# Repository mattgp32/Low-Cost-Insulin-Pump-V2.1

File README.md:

# Ultra Low-Cost Insulin Pump

This Git repository represents the final result of multiple design iterations of a low-cost insulin pump I have designed as part of my studies in medical device development. The repository contains files for hardware, both electrical and mechanical, and firmware. I have also included a BOM to make ordering of components easier if anyone wishes to replicate this design. The device has been tested in humans, in a small clinical trial, and a write-up of the results was published [here](https://pmc.ncbi.nlm.nih.gov/articles/PMC11292867/).

## Overview

The files for this device are split into four main areas: electrical hardware, mechanical hardware, android application, and firmware. This README contains a subsection for each of these aspects, including build instructions, initial setup, and usage. A complete exploded assembly for the device is shown in the image below:

### Electrical Hardware
PCB schematics and layout were created in KiCad, so you will need to install this to view/edit/order some assemblies. KiCad can be downloaded [here](https://www.kicad.org/download/). I added some components by hand to reduce costs; however I acknowledge not everyone would be comfortable to do so. Therefore, I'll be uploading an EasyEDA file soon which can be uploaded to JLCPCB, and allow you to order an assembled board more easily. Expect the total cost of an assembled board to be around US$30.

This PCB utilises an ESP32-S3 SOC as its MCU, and delivers the following key features for the low-cost pump:

1. Wireless communication via BLE
2. Stepper motor control thorugh interface with DRV8846
3. Li-Po charging through interface with MCP78371 through USB C 2.0
4. ADC monitoring of battery level 
5. ADC monitoring of linear potentiometer to determine position.
6. LEDs for user feedback and monitoring

#### Build Instructions

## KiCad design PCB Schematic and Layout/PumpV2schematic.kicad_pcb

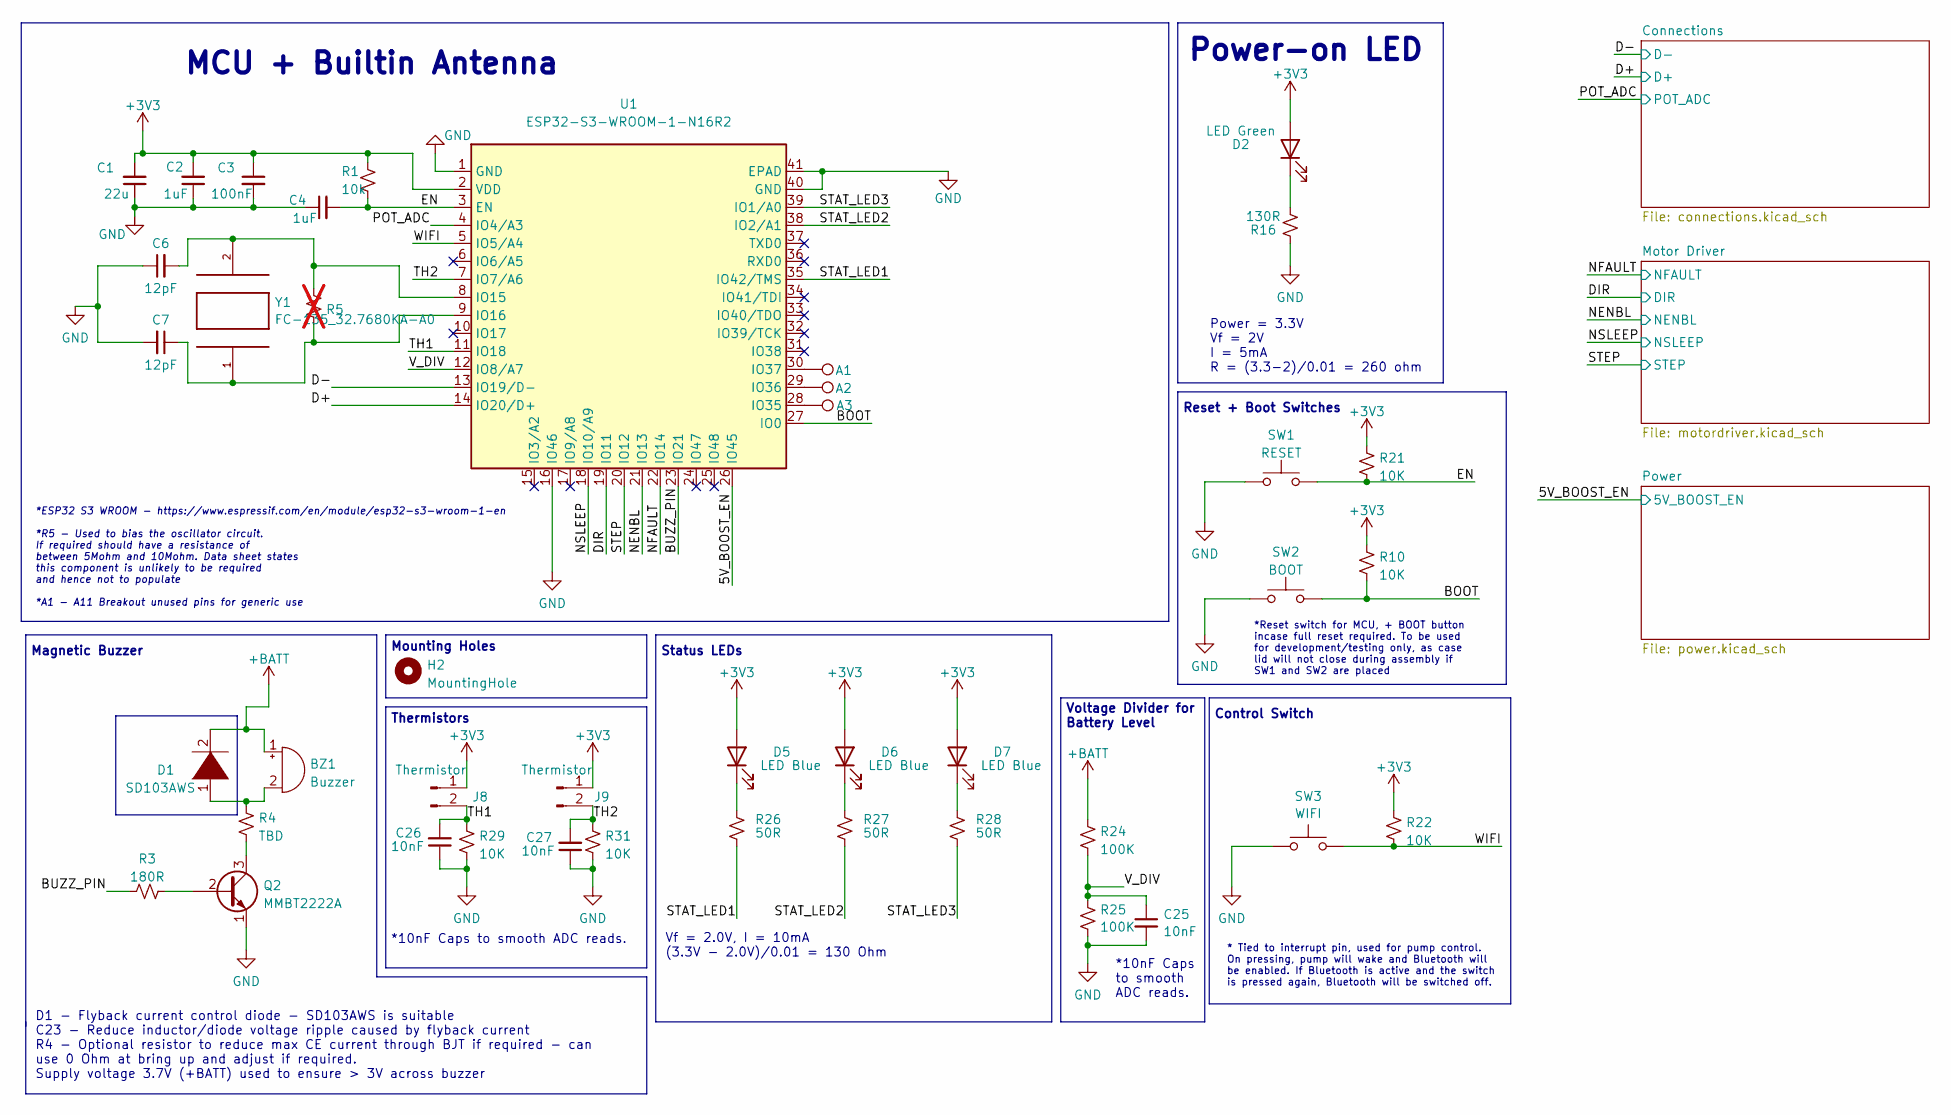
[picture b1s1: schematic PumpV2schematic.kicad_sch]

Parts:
A1, A2, A3: A0; TestPoint_THTPad_1.0x1.0mm_Drill0.5mm
BZ1: Buzzer; ST-0503 BUZZER
C1: 22u; C_0402_1005Metric; LCSC C2179118
C2, C4: 1uF; C_0402_1005Metric; LCSC C2887021
C3: 100nF; C_0402_1005Metric; LCSC C913614
C6, C7: 12pF; C_0402_1005Metric; LCSC C2235030
C25, C26, C27: 10nF; C_0402_1005Metric; LCSC C2167195
D1: SD103AWS; D_SOD-323; LCSC C181207
D2: LED Green; LED_0603_1608Metric; LCSC C84264
D5, D6, D7: LED Blue; LED_0603_1608Metric; LCSC C72041
H2: MountingHole; MountingHole_2.2mm_M2_ISO7380_Pad_TopBottom
J8, J9: Thermistor; PinHeader_1x02_P1.27mm_Vertical
Q2: MMBT2222A; SOT-23; LCSC C2891810
R1: 10k; R_0402_1005Metric; LCSC C25744
R3: 180R; R_0402_1005Metric; LCSC C911962
R4: TBD; R_0402_1005Metric; LCSC C17168
R5: TBD; R_0402_1005Metric; not fitted
R10, R21, R22, R29, R31: 10K; R_0402_1005Metric; LCSC C25744
R16: 130R; R_0402_1005Metric; LCSC C270649
R24, R25: 100K; R_0402_1005Metric; LCSC C319963
R26, R27, R28: 50R; R_0402_1005Metric; LCSC C477760
SW1: RESET; SW_DIP_SPSTx01_Slide_6.7x4.1mm_W6.73mm_P2.54mm_LowProfile_J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
SW2: BOOT; SW_DIP_SPSTx01_Slide_6.7x4.1mm_W6.73mm_P2.54mm_LowProfile_J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
SW3: WIFI; SW_DIP_SPSTx01_Slide_6.7x4.1mm_W6.73mm_P2.54mm_LowProfile_J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
U1: ESP32-S3-WROOM-1-N16R2; ESP32-S3-WROOM-1; LCSC C2913202
Y1: FC-135_32.7680KA-A0; XTAL_FC-135_32.7680KA-A0; LCSC C841881

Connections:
+3V3: C1.2, C2.2, C3.1, D2.2 (A), D5.2 (A), D6.2 (A), D7.2 (A), J8.1, J9.1, R1.1, R10.1, R21.1, R22.1, U1.2 (VDD); also elsewhere on the board
+BATT: BZ1.1 (-), D1.2 (A), R24.1; also elsewhere on the board
/5V_BOOST_EN: U1.26 (IO45); also elsewhere on the board
/BOOT: R10.2, SW2.2, U1.27 (IO0)
/BUZZ_PIN: R3.1, U1.23 (IO21)
/D+: U1.14 (IO20/D+); also elsewhere on the board
/D-: U1.13 (IO19/D-); also elsewhere on the board
/DIR: U1.19 (IO11); also elsewhere on the board
/EN: C4.2, R1.2, R21.2, SW1.2, U1.3 (EN)
/NENBL: U1.21 (IO13); also elsewhere on the board
/NFAULT: U1.22 (IO14); also elsewhere on the board
/NSLEEP: U1.18 (IO10/A9); also elsewhere on the board
/POT_ADC: U1.4 (IO4/A3); also elsewhere on the board
/STAT_LED1: R26.2, U1.35 (IO42/TMS)
/STAT_LED2: R27.2, U1.38 (IO2/A1)
/STAT_LED3: R28.2, U1.39 (IO1/A0)
/STEP: U1.20 (IO12); also elsewhere on the board
/TH1: C26.2, J8.2, R29.1, U1.11 (IO18)
/TH2: C27.2, J9.2, R31.1, U1.7 (IO7/A6)
/V_DIV: C25.1, R24.2, R25.1, U1.12 (IO8/A7)
/WIFI: R22.2, SW3.2, U1.5 (IO5/A4)
GND: C1.1, C2.1, C3.2, C4.1, C6.1, C7.2, C25.2, C26.1, C27.1, Q2.1 (E), R16.2, R25.2, R29.2, R31.2, SW1.1, SW2.1, SW3.1, U1.1 (GND), U1.16 (IO46), U1.40 (GND), U1.41 (EPAD); also elsewhere on the board
unnamed 24: BZ1.2 (+), D1.1 (K), R4.2; also elsewhere on the board
unnamed: D2.1 (K), R16.1
unnamed: D5.1 (K), R26.1
unnamed: D6.1 (K), R27.1
unnamed: D7.1 (K), R28.1
unnamed: Q2.2 (B), R3.2
unnamed: Q2.3 (C), R4.1
unnamed: C6.2, R5.1, U1.8 (IO15), Y1.2
unnamed: C7.1, R5.2, U1.9 (IO16), Y1.1
unnamed: A3.1, U1.28 (IO35)
unnamed: A2.1, U1.29 (IO36)
unnamed: A1.1, U1.30 (IO37)

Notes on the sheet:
Status LEDs
*10nF Caps to smooth ADC reads.
Magnetic Buzzer
Power = 3.3V Vf = 2V I = 5mA R = (3.3-2)/0.01 = 260 ohm
Reset + Boot Switches
*10nF Caps to smooth ADC reads.
MCU + Builtin Antenna
Thermistors
*ESP32 S3 WROOM - https://www.espressif.com/en/module/esp32-s3-wroom-1-en *R5 - Used to bias the oscillator circuit. If required should have a resistance of between 5Mohm and 10Mohm. Data sheet states this component is unlikely to be required and hence not to populate *A1 - A11 Breakout unused pins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
Vf = 2.0V, I = 10mA (3.3V - 2.0V)/0.01 = 130 Ohm
Voltage Divider for Battery Level
Power-on LED
* Tied to interrupt pin, used for pump control. On pressing, pump will wake and Bluetooth will be enabled. If Bluetooth is active and the switch is pressed again, Bluetooth will be switched off.
Control Switch
*Reset switch for MCU, + BOOT button incase full reset required. To be used for development/testing only, as case lid will not close during assembly if SW1 and SW2 are placed
Mounting Holes
D1 - Flyback current control diode - SD103AWS is suitable C23 - Reduce inductor/diode voltage ripple caused by flyback current R4 - Optional resistor to reduce max CE current through BJT if required - can use 0 Ohm at bring up and adjust if required. Supply voltage 3.7V (+BATT) used to ensure > 3V 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

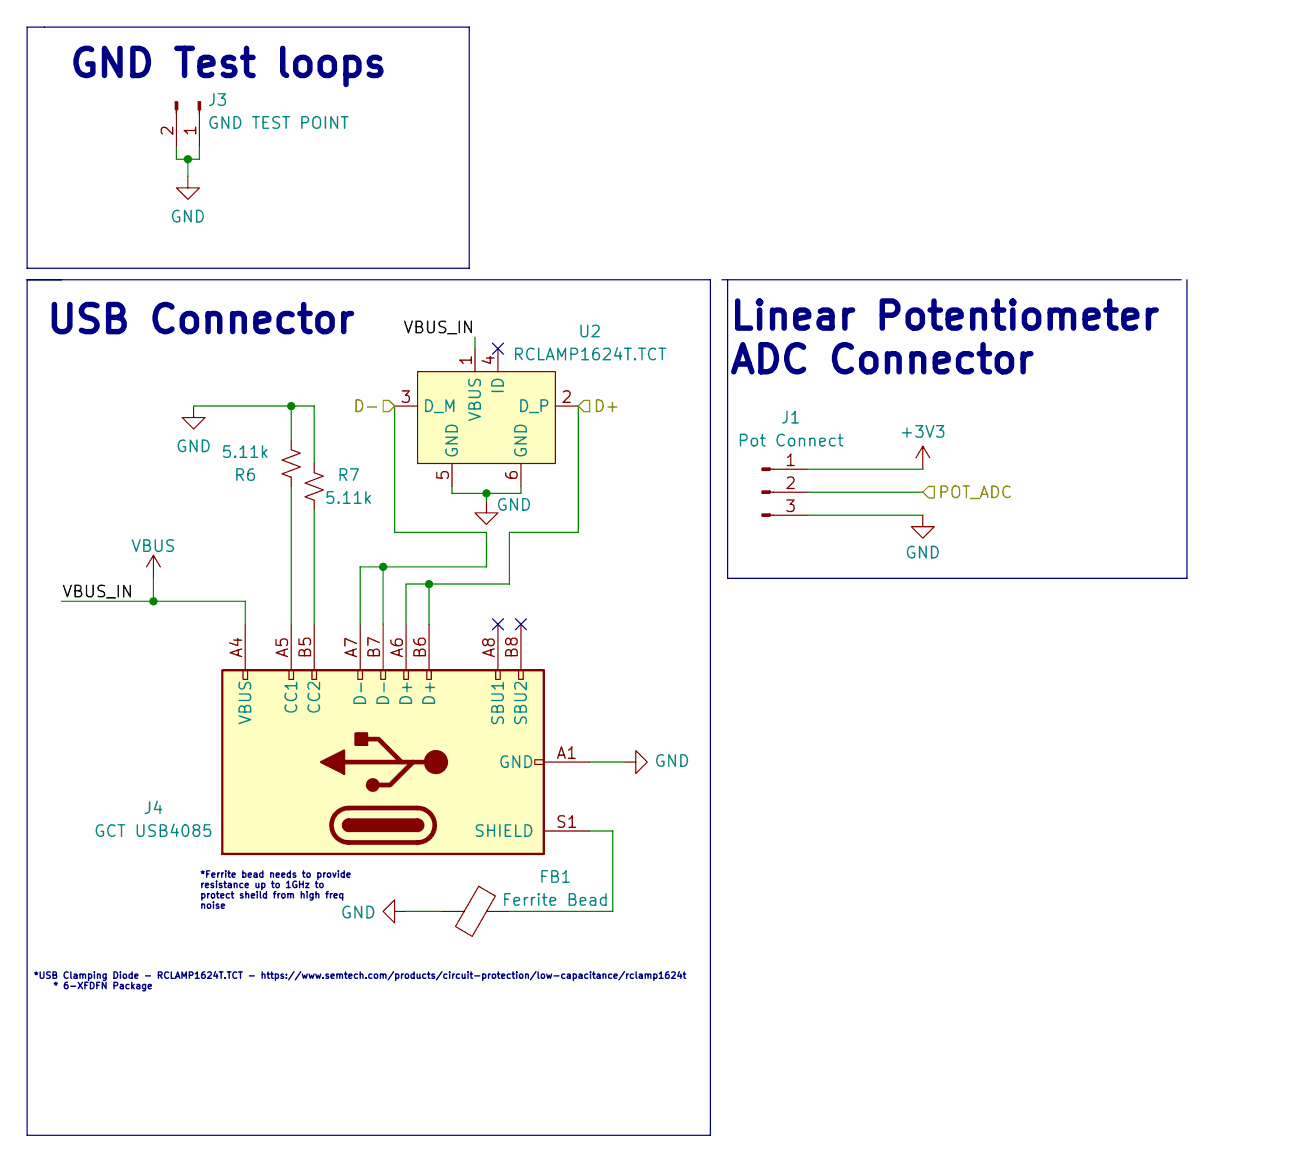
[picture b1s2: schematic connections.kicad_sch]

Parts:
FB1: Ferrite Bead; L_0402_1005Metric; LCSC C21516
J1: Pot Connect; PinHeader_1x03_P1.00mm_Vertical
J3: GND TEST POINT; PinHeader_1x02_P1.27mm_Vertical
J4: GCT USB4085; USB_C_Receptacle_GCT_USB4085
R6: 5.11k; R_0402_1005Metric; LCSC C310235
R7: 5.11k; R_0402_1005Metric
U2: RCLAMP1624T.TCT; SLP1710P4T; LCSC C1973485

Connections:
+3V3: J1.1; also elsewhere on the board
/D+: J4.A6 (D+), J4.B6 (D+), U2.2 (D_P); also elsewhere on the board
/D-: J4.A7 (D-), J4.B7 (D-), U2.3 (D_M); also elsewhere on the board
/POT_ADC: J1.2; also elsewhere on the board
GND: FB1.2, J1.3, J3.1, J3.2, J4.A1 (GND), J4.A12 (GND), J4.B1 (GND), J4.B12 (GND), R6.2, R7.2, U2.5 (GND), U2.6 (GND); also elsewhere on the board
unnamed: J4.A5 (CC1), R6.1
unnamed: J4.B5 (CC2), R7.1
unnamed: FB1.1, J4.S1 (SHIELD)
VBUS: J4.A4 (VBUS), J4.A9 (VBUS), J4.B4 (VBUS), J4.B9 (VBUS), U2.1 (VBUS); also elsewhere on the board

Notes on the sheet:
Linear Potentiometer ADC Connector
*USB Clamping Diode - RCLAMP1624T.TCT - https://www.semtech.com/products/circuit-protection/low-capacitance/rclamp1624t * 6-XFDFN Package
*Ferrite bead needs to provide resistance up to 1GHz to protect sheild from high freq noise
USB Connector
GND Test loops

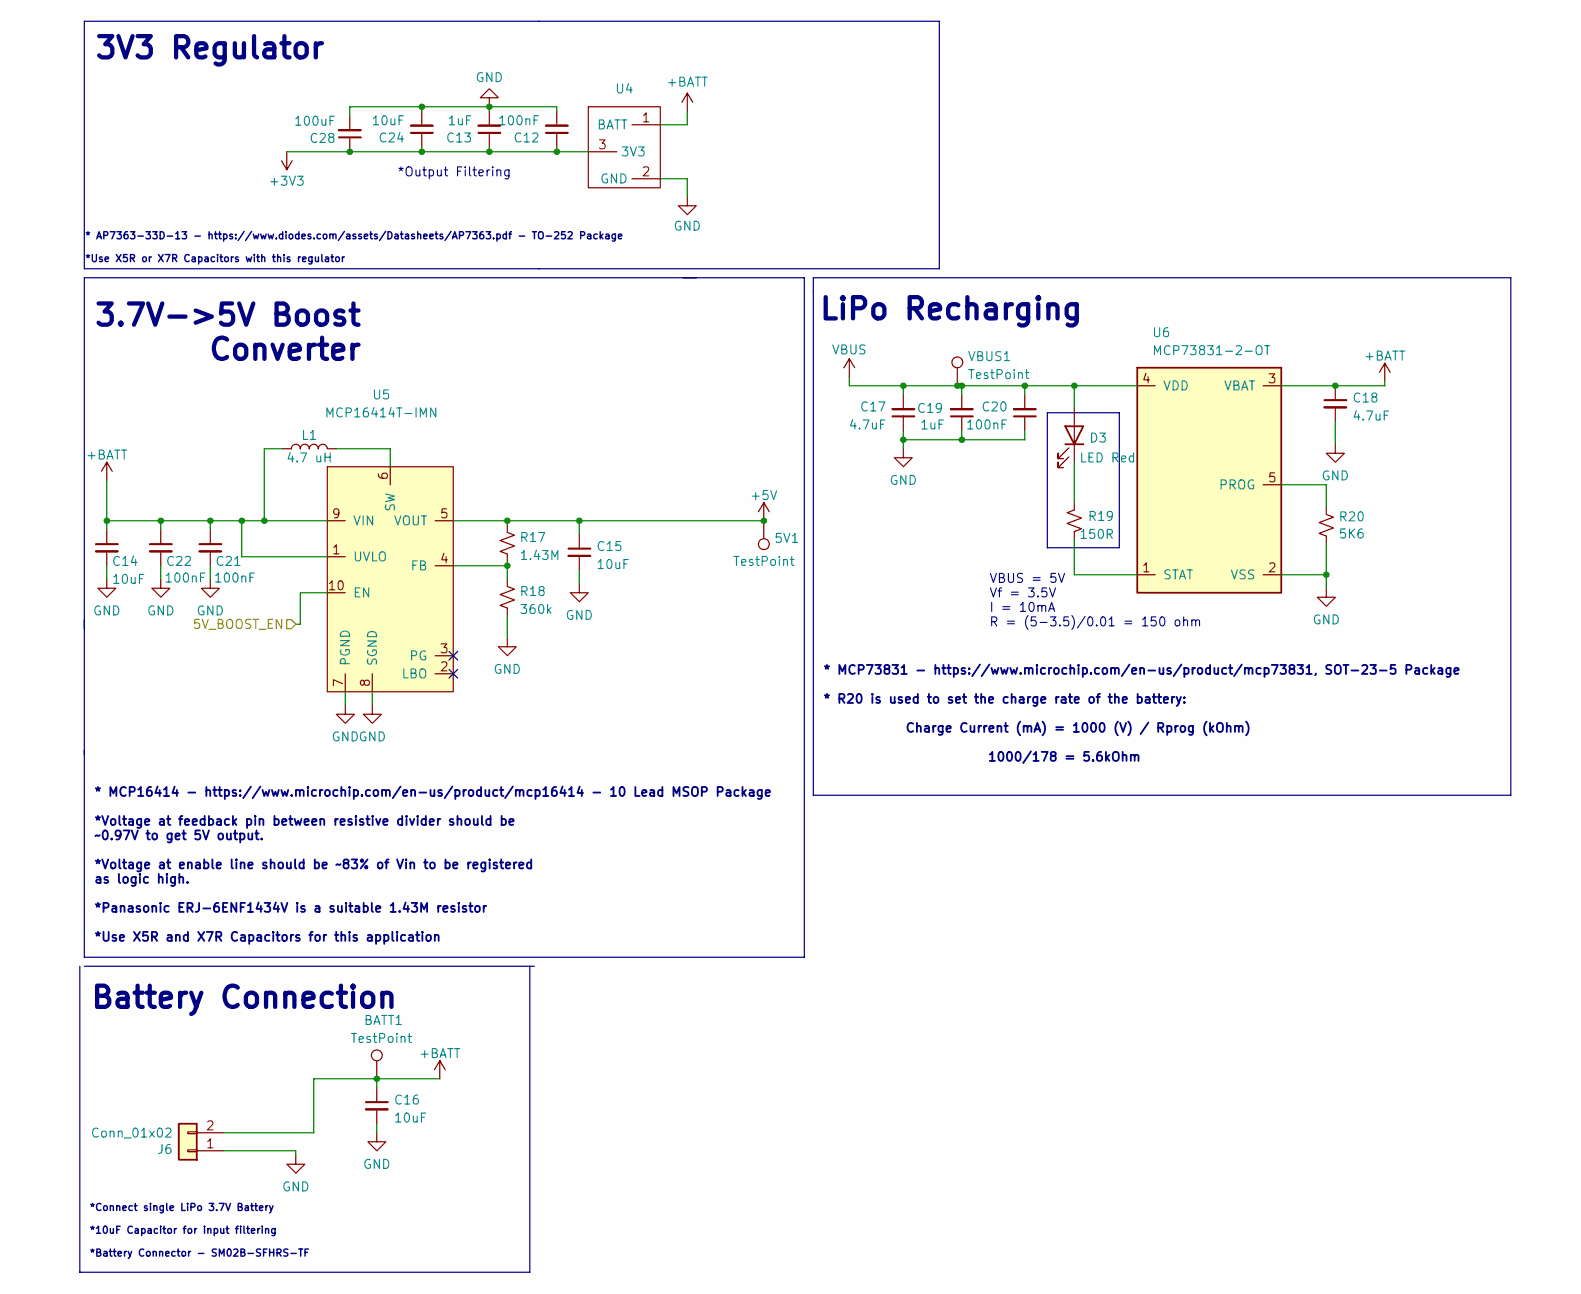
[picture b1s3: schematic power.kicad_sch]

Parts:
5V1: TestPoint; TestPoint_Pad_1.0x1.0mm
BATT1: TestPoint; TestPoint_Pad_1.0x1.0mm
C12, C20, C21, C22: 100nF; C_0402_1005Metric; LCSC C913614
C13, C19: 1uF; C_0402_1005Metric; LCSC C2887021
C14, C15, C16, C24: 10uF; C_0402_1005Metric; LCSC C1864622
C17, C18: 4.7uF; C_0402_1005Metric; LCSC C723999
C28: 100uF; C_1210_3225Metric; LCSC C2762605
D3: LED Red; LED_0603_1608Metric; LCSC C2286
J6: Conn_01x02; PinHeader_1x02_P1.27mm_Vertical
L1: 4.7 uH; L_1008_2520Metric; LCSC C2981204
R17: 1.43M; R_0402_1005Metric; LCSC C368342
R18: 360k; R_0402_1005Metric; LCSC C413117
R19: 150R; R_0402_1005Metric; LCSC C3015763
R20: 5K6; R_0402_1005Metric; LCSC C174239
U4: DPAK; LCSC C108723
U5: MCP16414T-IMN; SOP50P490X110-10N; LCSC C1518054
U6: MCP73831-2-OT; SOT-23-5; LCSC C625597
VBUS1: TestPoint; TestPoint_Pad_1.0x1.0mm

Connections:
+3V3: C12.1, C13.1, C24.1, C28.1, U4.3 (3V3); also elsewhere on the board
+5V: 5V1.1, C15.1, R17.1, U5.5 (VOUT); also elsewhere on the board
+BATT: BATT1.1, C14.1, C16.1, C18.1, C21.1, C22.1, J6.2, L1.1, U4.1 (BATT), U5.1 (UVLO), U5.9 (VIN), U6.3 (VBAT); also elsewhere on the board
/5V_BOOST_EN: U5.10 (EN); also elsewhere on the board
GND: C12.2, C13.2, C14.2, C15.2, C16.2, C17.1, C18.2, C19.1, C20.1, C21.2, C22.2, C24.2, C28.2, J6.1, R18.2, R20.2, U4.2 (GND), U5.7 (PGND), U5.8 (SGND), U6.2 (VSS); also elsewhere on the board
unnamed: D3.1 (K), R19.2
unnamed: R17.2, R18.1, U5.4 (FB)
unnamed: L1.2, U5.6 (SW)
unnamed: R20.1, U6.5 (PROG)
unnamed: R19.1, U6.1 (STAT)
VBUS: C17.2, C19.2, C20.2, D3.2 (A), U6.4 (VDD), VBUS1.1; also elsewhere on the board

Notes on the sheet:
* MCP73831 - https://www.microchip.com/en-us/product/mcp73831, SOT-23-5 Package * R20 is used to set the charge rate of the battery: Charge Current (mA) = 1000 (V) / Rprog (kOhm) 1000/178 = 5.6kOhm
* MCP16414 - https://www.microchip.com/en-us/product/mcp16414 - 10 Lead MSOP Package *Voltage at feedback pin between resistive divider should be ~0.97V to get 5V output. *Voltage at enable line should be ~83% of Vin to be registered as logic high. *Panasonic ERJ-6ENF1434V is a suitable 1.43M resis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
3V3 Regulator
LiPo Recharging
3.7V->5V Boost Converter
* AP7363-33D-13 - https://www.diodes.com/assets/Datasheets/AP7363.pdf - TO-252 Package *Use X5R or X7R Capacitors with this regulator
Battery Connection
*Output Filtering
*Connect single LiPo 3.7V Battery *10uF Capacitor for input filtering *Battery Connector - SM02B-SFHRS-TF
VBUS = 5V Vf = 3.5V I = 10mA R = (5-3.5)/0.01 = 150 ohm

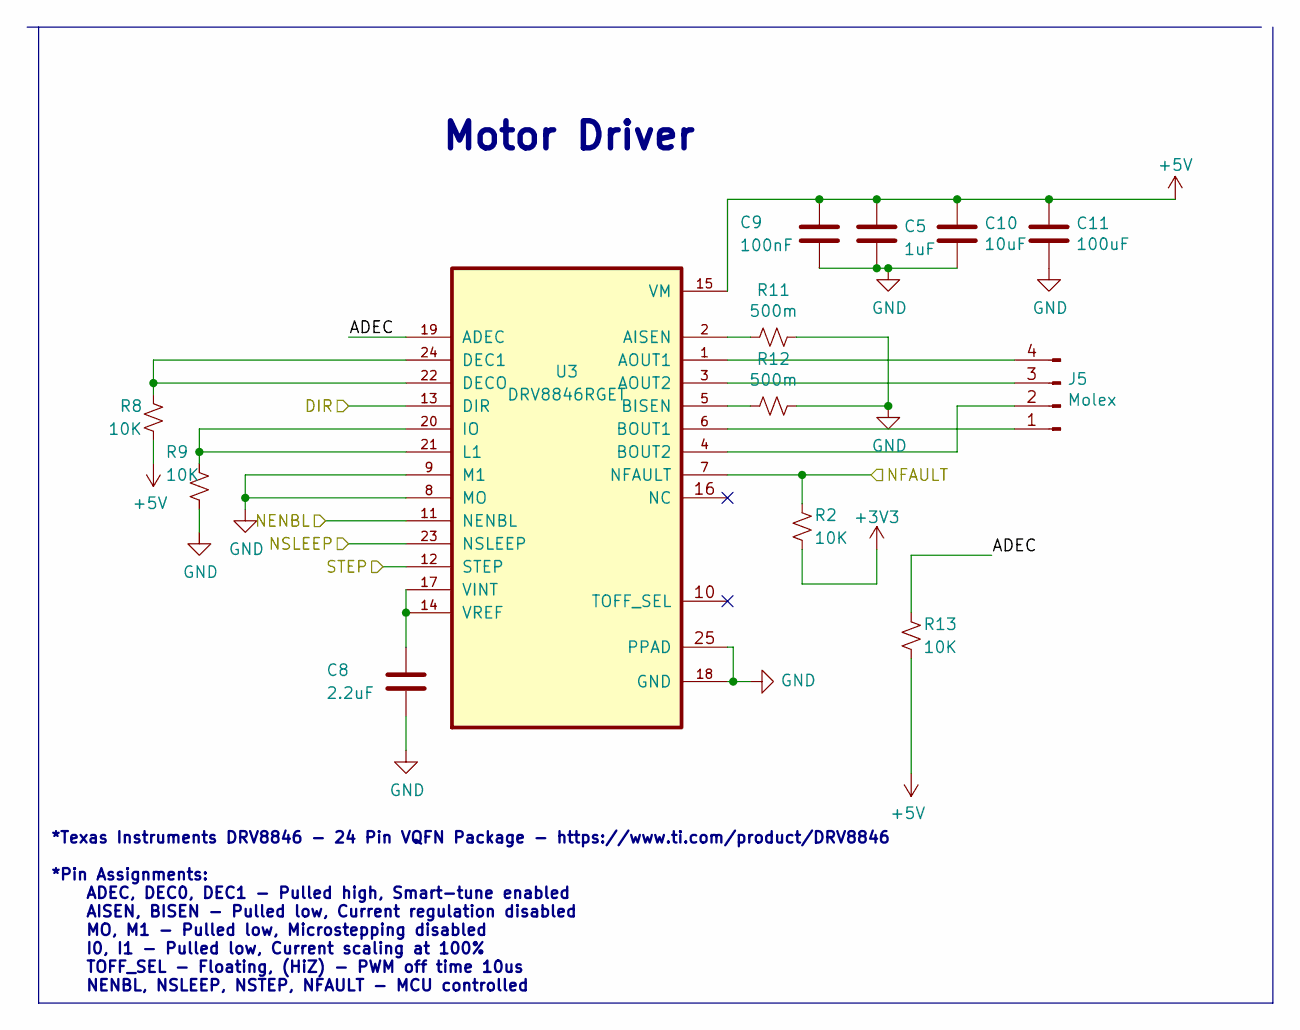
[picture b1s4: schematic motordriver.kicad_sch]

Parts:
C5: 1uF; C_0402_1005Metric; LCSC C2887021
C8: 2.2uF; C_0402_1005Metric; LCSC C710862
C9: 100nF; C_0402_1005Metric; LCSC C913614
C10: 10uF; C_0402_1005Metric; LCSC C1864622
C11: 100uF; C_1210_3225Metric; LCSC C2762605
J5: Molex; Hirose_DF13-04P-1.25DSA_1x04_P1.25mm_Vertical
R2, R8, R9, R13: 10K; R_0402_1005Metric; LCSC C25744
R11, R12: 500m; R_0402_1005Metric; LCSC C5204041
U3: DRV8846RGET; QFN50P400X400X100-25N; LCSC C473340

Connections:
+3V3: R2.2; also elsewhere on the board
+5V: C5.1, C9.1, C10.1, C11.1, R8.2, R13.2, U3.15 (VM); also elsewhere on the board
/DIR: U3.13 (DIR); also elsewhere on the board
/Motor Driver/ADEC: R13.1, U3.19 (ADEC)
/NENBL: U3.11 (NENBL); also elsewhere on the board
/NFAULT: R2.1, U3.7 (NFAULT); also elsewhere on the board
/NSLEEP: U3.23 (NSLEEP); also elsewhere on the board
/STEP: U3.12 (STEP); also elsewhere on the board
GND: C5.2, C8.2, C9.2, C10.2, C11.2, R9.2, R11.1, R12.1, U3.8 (MO), U3.9 (M1), U3.18 (GND), U3.25 (PPAD); also elsewhere on the board
unnamed: J5.1, U3.6 (BOUT1)
unnamed: J5.2, U3.4 (BOUT2)
unnamed: J5.3, U3.3 (AOUT2)
unnamed: J5.4, U3.1 (AOUT1)
unnamed: R11.2, U3.2 (AISEN)
unnamed: R12.2, U3.5 (BISEN)
unnamed: R8.1, U3.22 (DECO), U3.24 (DEC1)
unnamed: R9.1, U3.20 (IO), U3.21 (L1)
unnamed: C8.1, U3.14 (VREF), U3.17 (VINT)

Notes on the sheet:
Motor Driver
*Texas Instruments DRV8846 - 24 Pin VQFN Package - https://www.ti.com/product/DRV8846 *Pin Assignments: ADEC, DEC0, DEC1 - Pulled high, Smart-tune enabled AISEN, BISEN - Pulled low, Current regulation disabled MO, M1 - Pulled low, Microstepping disabled I0, I1 - Pulled low, Current scaling at 100% 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

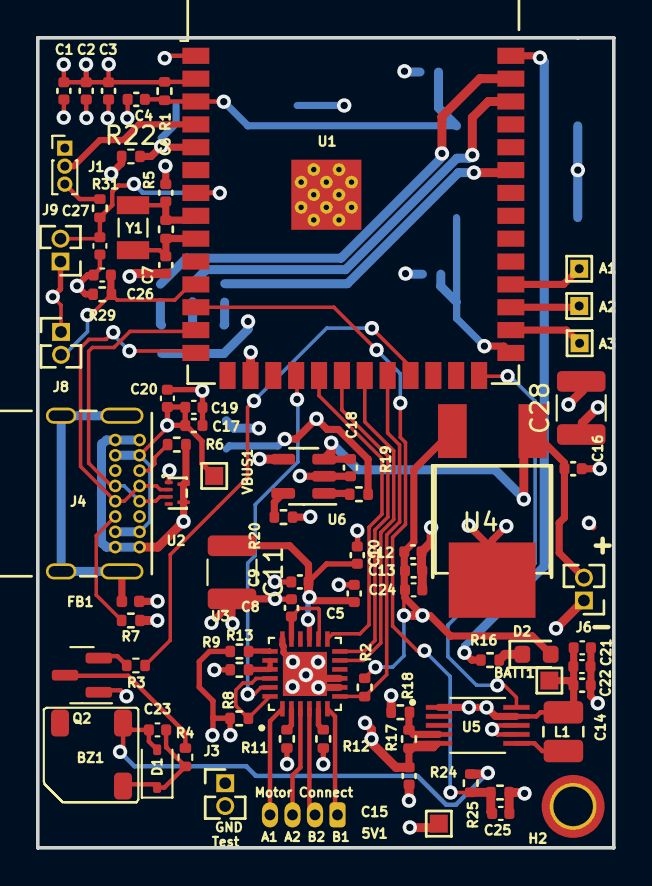
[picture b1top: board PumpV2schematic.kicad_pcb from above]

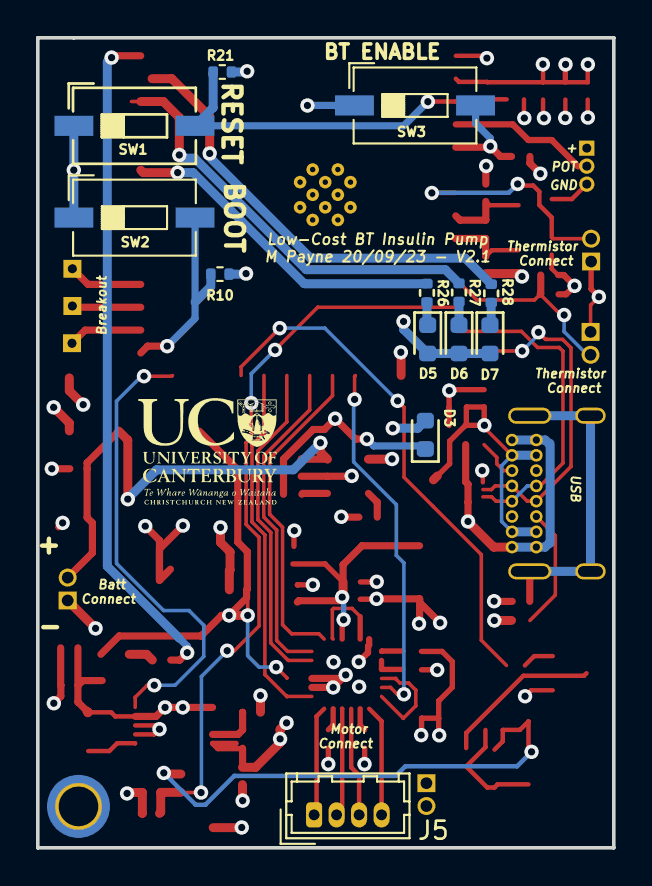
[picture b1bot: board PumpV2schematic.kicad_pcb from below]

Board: 4 copper layers, 32.0 x 45.0 mm, 89 parts (13 on the bottom side), 54 nets.

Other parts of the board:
C23: 1uF; C_0402_1005Metric

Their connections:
+BATT: C23.1; also elsewhere on the board
unnamed 24: C23.2; also elsewhere on the board

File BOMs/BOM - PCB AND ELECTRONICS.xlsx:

Reference | Value | Footprint | Qty | Unit Cost (USD) | Total Cost (USD) | Supplier | Supplier Part No.
BZ1 | Buzzer | Bluetooth Pump V2:ST-0503 BUZZER | 1 | 2.79 | 2.79 | Digikey | 433-1083-6-ND
C1 | 22uF | Capacitor_SMD:C_0402_1005Metric | 1 | 0.08 | 0.08 | Digikey | 587-1452-6-ND
C2,C4,C5,C13,C19 | 1uF | Capacitor_SMD:C_0402_1005Metric | 5 | 0.08 | 0.4 | Digikey | 587-1231-6-ND
C3,C9,C12,C20,C21,C22 | 100nF | Capacitor_SMD:C_0402_1005Metric | 6 | 0.1 | 0.60000000000000009 | Digikey | 1276-CL05B104KP5VPNCDKR-ND
C6,C7 | 12pF | Capacitor_SMD:C_0402_1005Metric | 2 | 0.15 | 0.3 | Digikey | 490-11190-6-ND
C8 | 2.2uF | Capacitor_SMD:C_0402_1005Metric | 1 | 0.08 | 0.08 | Digikey | 1276-1469-6-ND
C10,C14,C15,C16,C24 | 10uF | Capacitor_SMD:C_0402_1005Metric | 5 | 0.08 | 0.4 | Digikey | 1276-1450-6-ND
C11,C28 | 100uF | Capacitor_SMD:C_1210_3225Metric | 2 | 0.56999999999999995 | 1.1399999999999999 | Digikey | 490-10530-6-ND
C17,C18 | 4.7uF | Capacitor_SMD:C_0402_1005Metric | 2 | 0.08 | 0.16 | Digikey | 1276-1481-6-ND
C25,C26,C27 | 10nF | Capacitor_SMD:C_0402_1005Metric | 3 | 0.1 | 0.30000000000000004 | Digikey | 399-C0402C103K4REC7411DKR-ND
D1 | SD103AWS | Diode_SMD:D_SOD-323 | 1 | 0.11 | 0.11 | Digikey | 4530-SD103AWSDKR-ND
D2 | LED Green | LED_SMD:LED_0603_1608Metric | 1 | 0.15 | 0.15 | Digikey | 732-4980-6-ND
D3 | LED Red | LED_SMD:LED_0603_1608Metric | 1 | 0.15 | 0.15 | Digikey | 732-4978-6-ND
D5,D6,D7 | LED Blue | LED_SMD:LED_0603_1608Metric | 3 | 0.15 | 0.44999999999999996 | Digikey | 732-4966-6-ND
FB1 | Ferrite Bead | Inductor_SMD:L_0402_1005Metric | 1 | 0.16 | 0.16 | Digikey | 3442-MZAH1005F101-1R1TFDKR-ND
J4 | GCT USB4085 | Connector_USB:USB_C_Receptacle_GCT_USB4085 | 1 | 0.88 | 0.88 | Digikey | 2073-USB4085-GF-ADKR-ND
J5 | Molex | Connector_Hirose:Hirose_DF13-04P-1.25DSA_1x04_P1.25mm_Vertical | 1 | 0.27 | 0.27 | Digikey | WM1733-ND
J6 | Conn_01x02 | Connector_PinHeader_1.27mm:PinHeader_1x02_P1.27mm_Vertical | 1 | 0.39 | 0.39 | Digikey | 455-1788-6-ND
J8,J9 | Thermistor | Connector_PinHeader_1.27mm:PinHeader_1x02_P1.27mm_Vertical | 2 | 0.53 | 1.06 | Digikey | 5666-103JG1J-ND
L1 | 4.7 uH | Inductor_SMD:L_1008_2520Metric | 1 | 0.16 | 0.16 | Digikey | 587-3228-6-ND
Q2 | MMBT2222A | Package_TO_SOT_SMD:SOT-23 | 1 | 0.46 | 0.46 | Digikey | 846-DTD543EE3TLDKR-ND
R1,R2,R8,R9,R10,R13,R21,R22,R29,R31 | 10K | Resistor_SMD:R_0402_1005Metric | 10 | 3.9E-2 | 0.39 | Digikey | 1276-3431-6-ND
R3 | 180R | Resistor_SMD:R_0402_1005Metric | 1 | 0.1 | 0.1 | Digikey | A129618DKR-ND
R4,R5 | 0R | Resistor_SMD:R_0402_1005Metric | 2 | 0.1 | 0.2 | Digikey | P0.0JDKR-ND
R6,R7 | 5.11k | Resistor_SMD:R_0402_1005Metric | 2 | 0.1 | 0.2 | Digikey | 311-5.11KLRDKR-ND
R11,R12 | 500m | Resistor_SMD:R_0402_1005Metric | 2 | 0.28000000000000003 | 0.56000000000000005 | Digikey | 13-PT0402FR-070R5LDKR-ND
R16 | 130R | Resistor_SMD:R_0402_1005Metric | 1 | 0.1 | 0.1 | Digikey | RMCF0402FT130RDKR-ND
R17 | 1.43M | Resistor_SMD:R_0402_1005Metric | 1 | 0.1 | 0.1 | Digikey | 13-RC0402FR-071M43LDKR-ND
R18 | 360k | Resistor_SMD:R_0402_1005Metric | 1 | 0.1 | 0.1 | Digikey | 311-360KLRDKR-ND
R19 | 150R | Resistor_SMD:R_0402_1005Metric | 1 | 0.1 | 0.1 | Digikey | 311-150LRDKR-ND
R20 | 5K6 | Resistor_SMD:R_0402_1005Metric | 1 | 0.1 | 0.1 | Digikey | 311-5.6KLRDKR-ND
R24,R25 | 100K | Resistor_SMD:R_0402_1005Metric | 2 | 0.1 | 0.2 | Digikey | 311-100KJRDKR-ND
R26,R27,R28 | 50R | Resistor_SMD:R_0402_1005Metric | 3 | 0.18 | 0.54 | Digikey | 13-RT0402BRE0750RLDKR-ND
SW1 | RESET | Button_Switch_SMD:SW_DIP_SPSTx01_Slide_6.7x4.1mm_W6.73mm_P2.54mm_LowProfile_JPin | 1 | 0.24 | 0.24 | Digikey | CKN12330-6-ND
SW2 | BOOT | Button_Switch_SMD:SW_DIP_SPSTx01_Slide_6.7x4.1mm_W6.73mm_P2.54mm_LowProfile_JPin | 1 | 0.24 | 0.24 | Digikey | CKN12330-6-ND
SW3 | WIFI | Button_Switch_SMD:SW_DIP_SPSTx01_Slide_6.7x4.1mm_W6.73mm_P2.54mm_LowProfile_JPin | 1 | 0.24 | 0.24 | Digikey | CKN12330-6-ND
U1 | ESP32-S3-WROOM-1-N16R2 | GlucoseWatchFootprints:ESP32-S3-WROOM-1 | 1 | 6.13 | 6.13 | Digikey | 5407-ESP32-S3-WROOM-1-N16R2DKR-ND
U2 | RCLAMP1624T.TCT | GlucoseWatchFootprints:SLP1710P4T | 1 | 1.68 | 1.68 | Digikey | RCLAMP1624TTCTDKR-ND
U3 | DRV8846RGET | DRV8846RGET:QFN50P400X400X100-25N | 1 | 2.66 | 2.66 | Digikey | 296-40083-6-ND
U4 | ~ | Bluetooth Pump V2:DPAK | 1 | 0.94 | 0.94 | Digikey | AP7363-33D-13DKR-ND
U5 | MCP16414T-IMN | SOP50P490X110-10N:SOP50P490X110-10N | 1 | 0.85 | 0.85 | Digikey | 150-MCP16414T-I/UNDKR-ND
U6 | MCP73831-2-OT | Package_TO_SOT_SMD:SOT-23-5 | 1 | 0.76 | 0.76 | Digikey | MCP73831T-2DCI/OTDKR-ND
Y1 | FC-135_32.7680KA-A0 | FC-135_32.7680KA-A0:XTAL_FC-135_32.7680KA-A0 | 1 | 1.24 | 1.24 | Digikey | 535-13425-6-ND
Battery Connector | 02SR-3S | N/A | 1 | 0.23 | 0.23 | Digikey | 455-2183-ND
Slide Potentiometer | PTL20-15G1-203B2 | N/A | 1 | 2.46 | 2.46 | Digikey | PTL20-15G1-203B2-ND
Stepper Motor | CHS-GM12-10BY (Ratio 298:1, M4*55mm) | N/A | 1 | 9.9 | 9.9 | Alibaba | ChiHai Motor CHS-GM12-10BY
PCB Manufacture | JLCPCB | N/A | 1 | 0.7 | 0.7 | JLCPCB | N/A
LiPo-Battery | Emax 1S 3.8V 450mAh 80/160c HV | N/A | 1 | 8.36 | 8.36 | Hobby Station NZ | 1s45080c
 |  |  |  | TOTAL | 49.810000000000009

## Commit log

2023-04-18 pump has both basal and bolus functionality now
2023-05-01 pump has basal and bolus functionaity, connects to app and gives feedback throiugh LED flashes
2023-07-18 WIP Commit - Updating to Standardised Structure and Repeatable Build ENV
2023-08-03 Finish Updating Repo To Use Standard Practices
2023-11-15 Undo Accidental Merge
2023-11-15 Remove build files from repo
2023-11-28 Fix Build Issues with BT Configuration
2023-12-03 Add Pot Functionality incl Rewind and Prime
2023-12-04 Removed rtc.c because duplicate file, added buttons module, next step get bottun isr working
2023-12-05 Button interrupt and debounce working but reinitialising bluetooth causes a reset
2023-12-05 sleep mode sort of works, ironing out bugs
2023-12-05 Provisional code for trial - seems to work...
2023-12-06 Updated app to latest version, squashed a bug that undercalculated insulin deliveries.
    This is now essentially (bar minor changes) the code I will take to trial. has not failed any tests so far and seems to be relatively light on battery
2023-12-07 throttled cpu speed a little to save a few mAh
2023-12-08 seems to have a bug which can cause CPU to lock up after a random amount of time
2023-12-08 Added tons of print statements and deconfigured tickless idle
2023-12-08 Rewind function doesnt work otherwise
2023-12-08 Update Module Descriptors and Improve Project Readability
2023-12-08 Update sdkconfig for removed modules
2023-12-08 Get Mass Storage Enumerating Without Other Modules Enabled
2023-12-08 Move Phone App Into Its Own Folder
2023-12-09 Move Components into Appropriate Folder Structure +Get Project Building
2023-12-09 Add Standard Module Headers, Organize, + Fix Additional Build Issues
2023-12-09 Update + Standardize Function Naming Convention
2023-12-09 Extract Buzzer Functions From LED Module
2023-12-09 Extract Button Functions From Main
2023-12-09 Update System Functionality
2023-12-09 Generic Updates
2023-12-09 Restore Bluetooth Module Name
2023-12-09 Misc Minor Updates
2023-12-09 Resolve Merge Issues
2023-12-10 Update Comments to Understand What's Been Changed
2023-12-10 Streamline Functions and Fix Resources Allocation/Control Bugs
2023-12-10 Hardware files and most up to date software
2023-12-10 update after pushing on other machine
2023-12-10 Implemented fctn which sleeps and wake up perioically to clear any tasks waiting to run. Needs long term testing
2023-12-10 Add Error Logging Functionality
2023-12-10 Import Pump Hardware Into Repo
2023-12-10 Simplify Button Logic And Remove Additional RTOS Task
2023-12-11 WIP Commit
2023-12-11 WIP Commit 2
2023-12-11 Develop Branch ready for Matt
2023-12-11 Added my low power stuff, Did not do extesive testing but pup does successfully wake up and flash leds/turn motor. Also possible to wake up with button. Tried to keep code in same neat style as since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
2023-12-13 Add Safety Interlocks To Ensure Motor Wont Drive Past Limits
2023-12-13 Change to the 12S Sleep Timer
2023-12-13 Stop Tracking managed_component dir
2023-12-13 Fix Some USB Enumeration Issues
2023-12-15 Implement Logging Functionality
2025-01-13 Add aia file for insulin pump app
2025-05-21 Added BOMs for electrical and mechanical hardware
2025-05-21 Add BOM files, and mech and PCB hardware files
2025-05-26 Edit and push hardware files back to the repo
2025-05-26 Added readme images folder and exploded view image
2025-05-26 updates filepaths for readme to remove spaces
